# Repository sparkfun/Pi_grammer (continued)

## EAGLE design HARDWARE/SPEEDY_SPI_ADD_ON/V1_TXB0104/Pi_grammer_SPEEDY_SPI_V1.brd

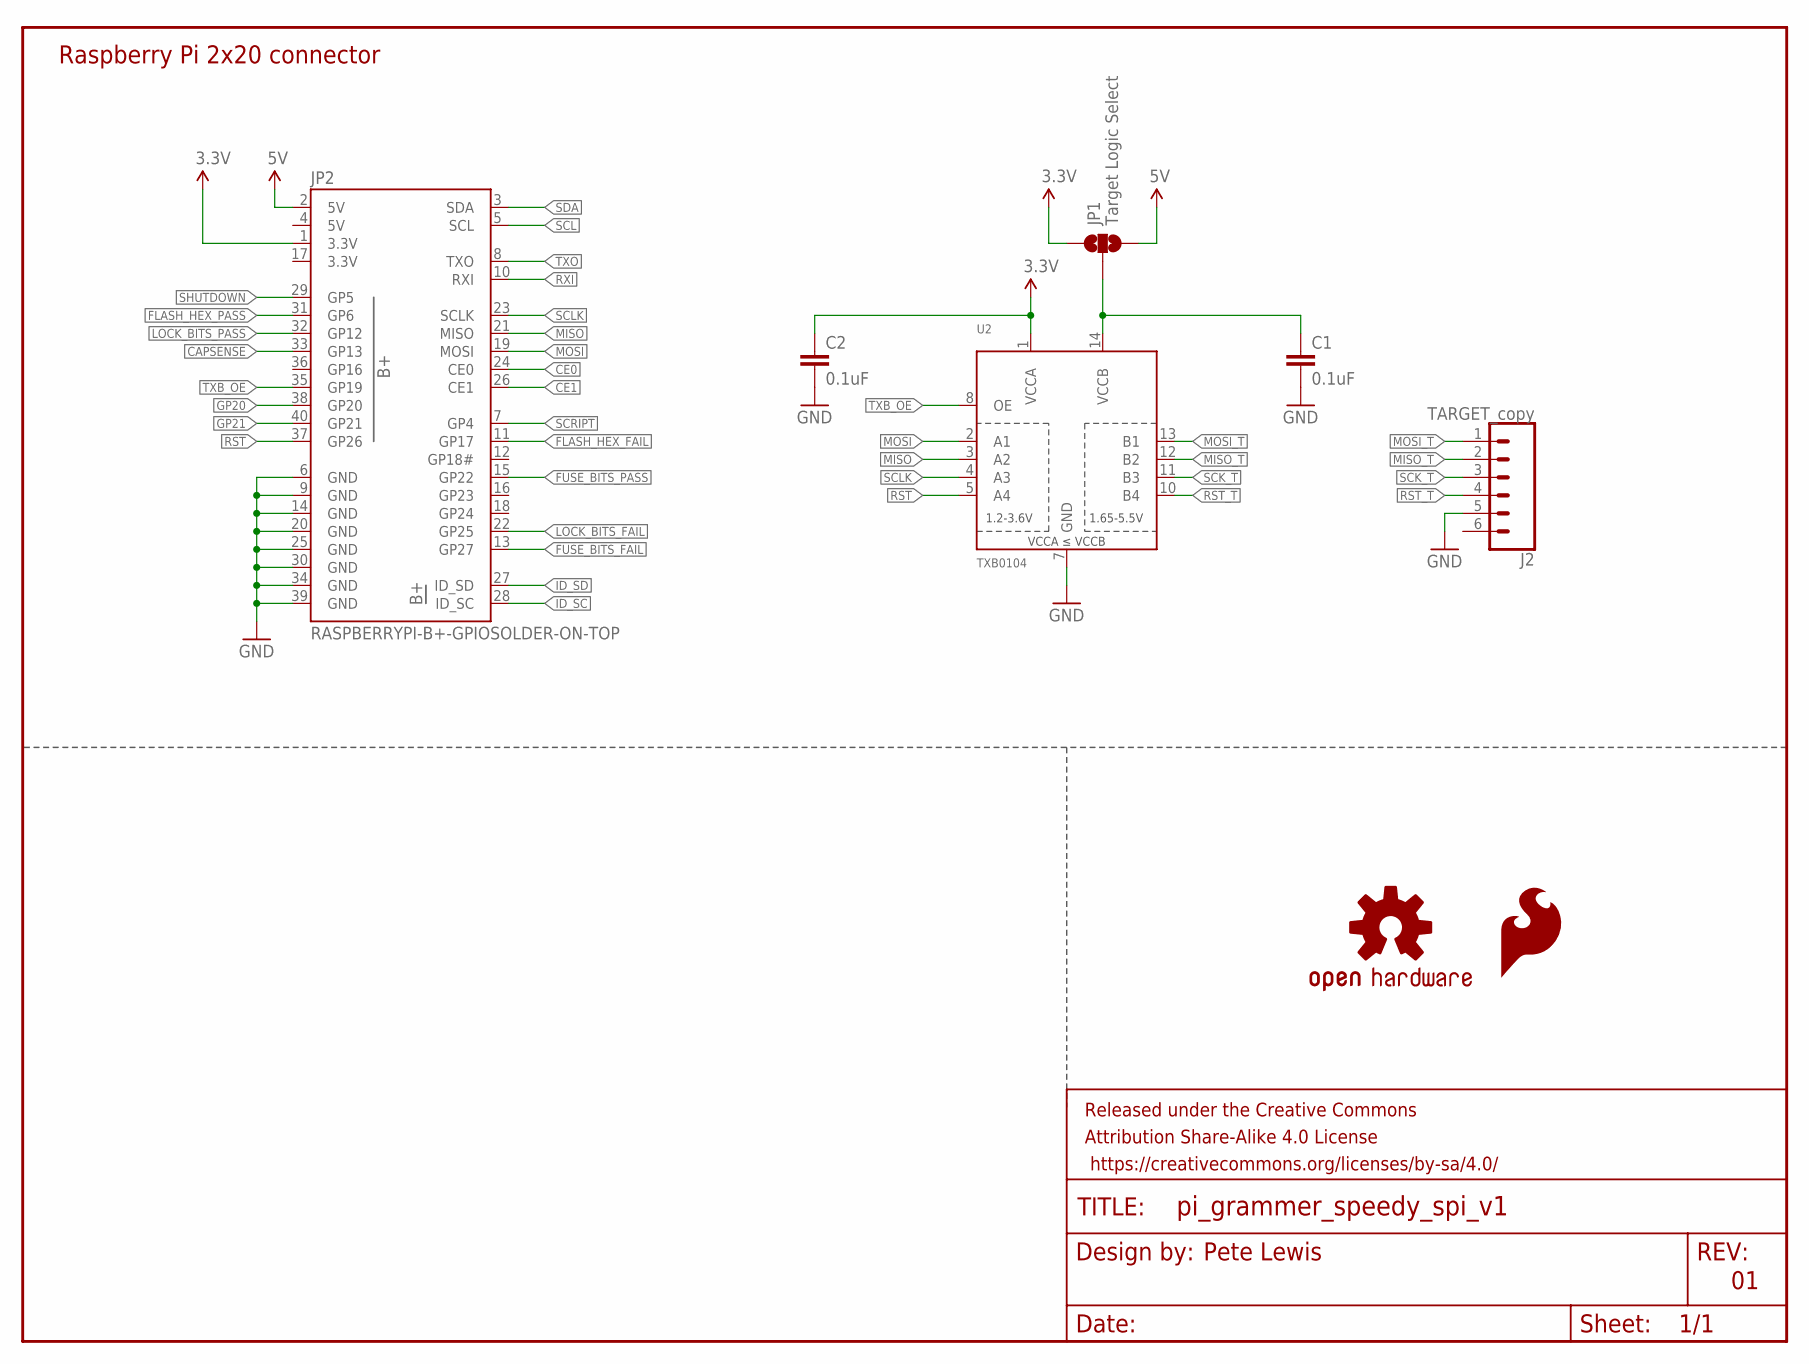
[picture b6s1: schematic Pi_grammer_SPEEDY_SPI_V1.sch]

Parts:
C1, C2: 0.1uF; 0603
FRAME1: FRAME-LETTER; CREATIVE_COMMONS
J2: TARGET_copy; MOLEX-1X6
JP1: Target Logic Select; SMT-JUMPER_3_NO_SILK
JP2: RASPBERRYPI-B+-GPIOSOLDER-ON-TOP; 2X20-SHROUDED-SOLDER-ON-TOP
LOGO1: SFE_LOGO_FLAME.1_INCH; SFE_LOGO_FLAME_.1
LOGO2: OSHW-LOGOS; OSHW-LOGO-S
U2: TXB0104; SO14

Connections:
3.3V: C2.1, JP1.1, JP2.1 (3.3V), JP2.17 (3.3V), U2.1 (VCCA)
5V: JP1.3, JP2.2 (5V), JP2.4 (5V)
CAPSENSE: JP2.33 (GP13)
CE0: JP2.24 (CE0)
CE1: JP2.26 (CE1)
FLASH_HEX_FAIL: JP2.11 (GP17)
FLASH_HEX_PASS: JP2.31 (GP6)
FUSE_BITS_FAIL: JP2.13 (GP27)
FUSE_BITS_PASS: JP2.15 (GP22)
GND: C1.2, C2.2, J2.5, JP2.6 (GND), JP2.9 (GND), JP2.14 (GND), JP2.20 (GND), JP2.25 (GND), JP2.30 (GND), JP2.34 (GND), JP2.39 (GND), U2.7 (GND)
GP20: JP2.38 (GP20)
GP21: JP2.40 (GP21)
ID_SC: JP2.28 (ID_SC)
ID_SD: JP2.27 (ID_SD)
LOCK_BITS_FAIL: JP2.22 (GP25)
LOCK_BITS_PASS: JP2.32 (GP12)
MISO: JP2.21 (MISO), U2.3 (A2)
MISO_T: J2.2, U2.12 (B2)
MOSI: JP2.19 (MOSI), U2.2 (A1)
MOSI_T: J2.1, U2.13 (B1)
unnamed: C1.1, JP1.2, U2.14 (VCCB)
RST: JP2.37 (GP26), U2.5 (A4)
RST_T: J2.4, U2.10 (B4)
RXI: JP2.10 (RXI)
SCK_T: J2.3, U2.11 (B3)
SCL: JP2.5 (SCL)
SCLK: JP2.23 (SCLK), U2.4 (A3)
SCRIPT: JP2.7 (GP4)
SDA: JP2.3 (SDA)
SHUTDOWN: JP2.29 (GP5)
TXB_OE: JP2.35 (GP19), U2.8 (OE)
TXO: JP2.8 (TXO)

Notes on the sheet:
Raspberry Pi 2x20 connector
Pete Lewis

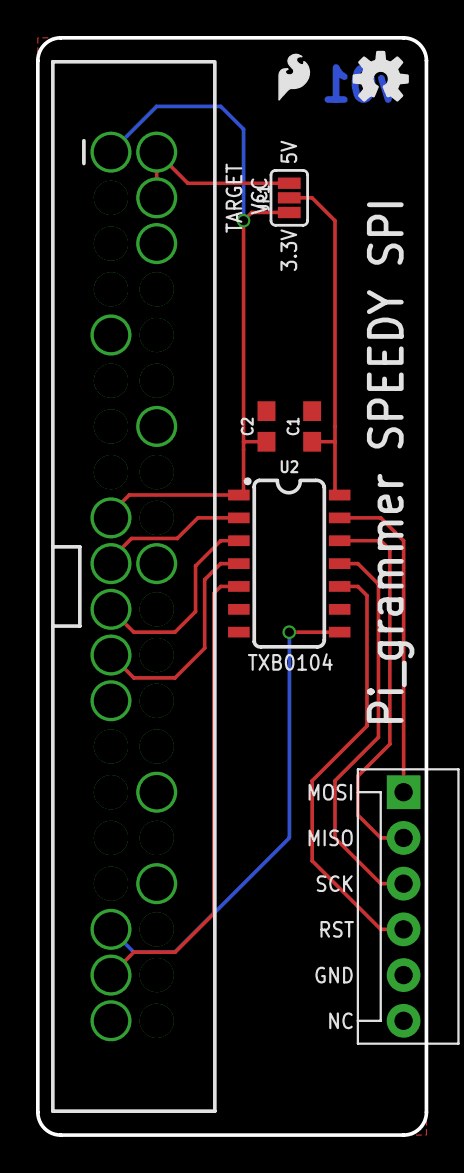
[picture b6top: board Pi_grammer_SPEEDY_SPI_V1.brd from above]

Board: 2 copper layers, 21.6 x 61.0 mm, 9 parts (0 on the bottom side), 13 nets.

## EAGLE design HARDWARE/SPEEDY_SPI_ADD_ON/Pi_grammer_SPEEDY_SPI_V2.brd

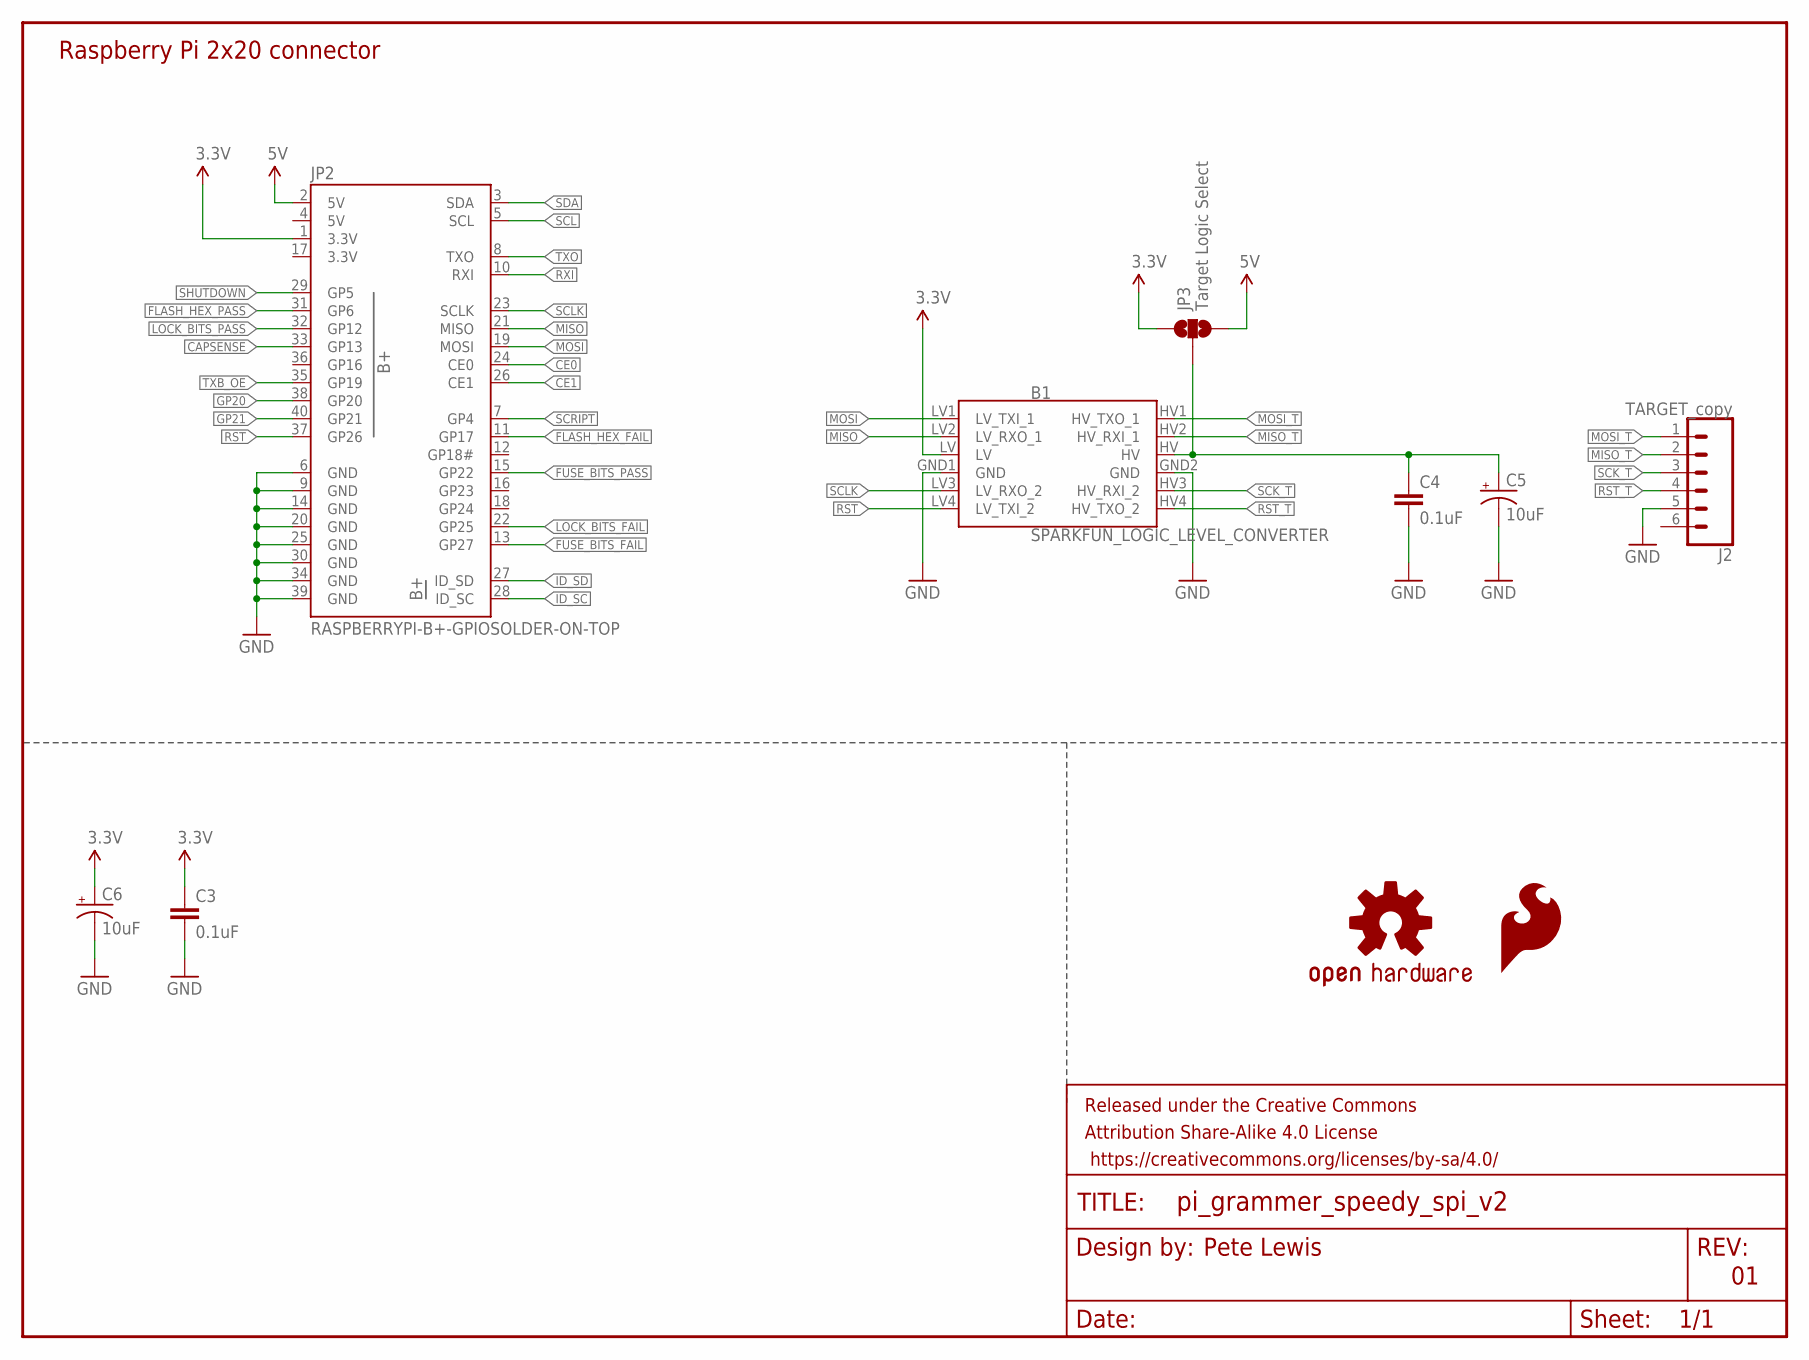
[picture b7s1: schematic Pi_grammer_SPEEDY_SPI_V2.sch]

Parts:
B1: SPARKFUN_LOGIC_LEVEL_CONVERTER
C3, C4: 0.1uF; 0603
C5, C6: 10uF; EIA3216
FRAME1: FRAME-LETTER; CREATIVE_COMMONS
J2: TARGET_copy; MOLEX-1X6_LOCK
JP2: RASPBERRYPI-B+-GPIOSOLDER-ON-TOP; 2X20-SHROUDED-SOLDER-ON-TOP
JP3: Target Logic Select; SMT-JUMPER_3_NO_SILK
LOGO1: SFE_LOGO_FLAME.1_INCH; SFE_LOGO_FLAME_.1
LOGO2: OSHW-LOGOS; OSHW-LOGO-S

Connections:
3.3V: B1.LV, C3.1, C6.+, JP2.1 (3.3V), JP2.17 (3.3V), JP3.1
5V: JP2.2 (5V), JP2.4 (5V), JP3.3
CAPSENSE: JP2.33 (GP13)
CE0: JP2.24 (CE0)
CE1: JP2.26 (CE1)
FLASH_HEX_FAIL: JP2.11 (GP17)
FLASH_HEX_PASS: JP2.31 (GP6)
FUSE_BITS_FAIL: JP2.13 (GP27)
FUSE_BITS_PASS: JP2.15 (GP22)
GND: B1.GND1 (GND), B1.GND2 (GND), C3.2, C4.2, C5.-, C6.-, J2.5, JP2.6 (GND), JP2.9 (GND), JP2.14 (GND), JP2.20 (GND), JP2.25 (GND), JP2.30 (GND), JP2.34 (GND), JP2.39 (GND)
GP20: JP2.38 (GP20)
GP21: JP2.40 (GP21)
ID_SC: JP2.28 (ID_SC)
ID_SD: JP2.27 (ID_SD)
LOCK_BITS_FAIL: JP2.22 (GP25)
LOCK_BITS_PASS: JP2.32 (GP12)
MISO: B1.LV2 (LV_RXO_1), JP2.21 (MISO)
MISO_T: B1.HV2 (HV_RXI_1), J2.2
MOSI: B1.LV1 (LV_TXI_1), JP2.19 (MOSI)
MOSI_T: B1.HV1 (HV_TXO_1), J2.1
unnamed: B1.HV, C4.1, C5.+, JP3.2
RST: B1.LV4 (LV_TXI_2), JP2.37 (GP26)
RST_T: B1.HV4 (HV_TXO_2), J2.4
RXI: JP2.10 (RXI)
SCK_T: B1.HV3 (HV_RXI_2), J2.3
SCL: JP2.5 (SCL)
SCLK: B1.LV3 (LV_RXO_2), JP2.23 (SCLK)
SCRIPT: JP2.7 (GP4)
SDA: JP2.3 (SDA)
SHUTDOWN: JP2.29 (GP5)
TXB_OE: JP2.35 (GP19)
TXO: JP2.8 (TXO)

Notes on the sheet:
Raspberry Pi 2x20 connector
Pete Lewis

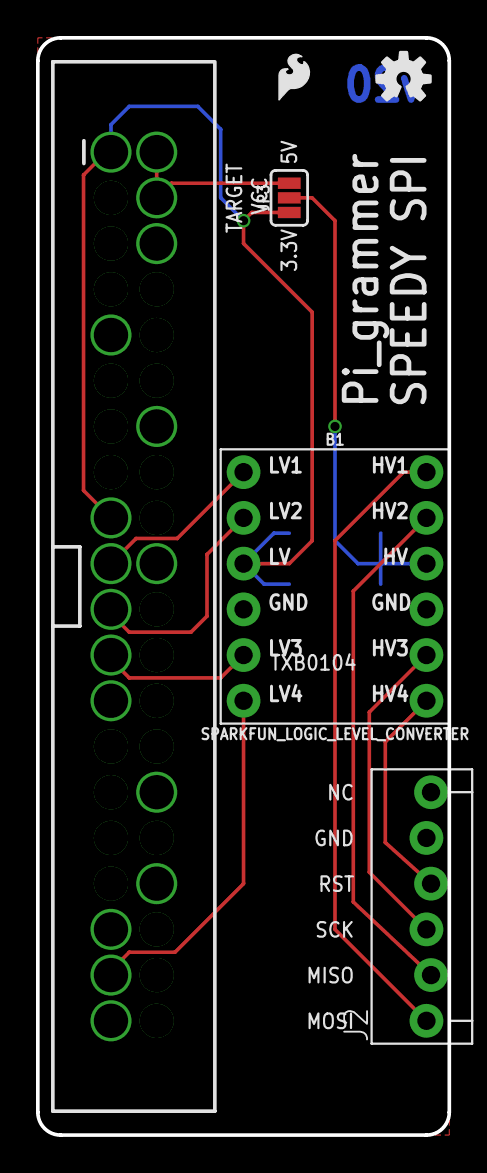
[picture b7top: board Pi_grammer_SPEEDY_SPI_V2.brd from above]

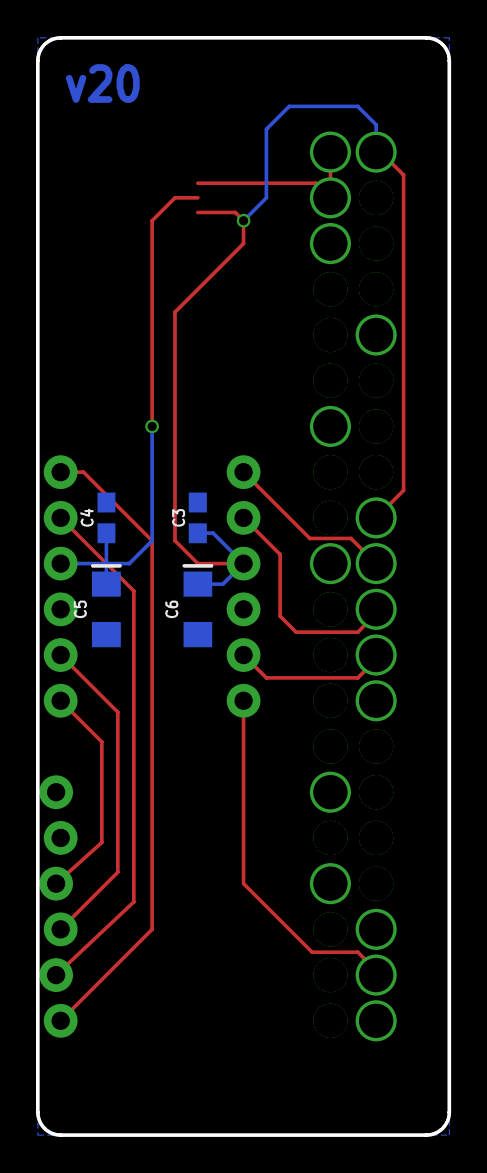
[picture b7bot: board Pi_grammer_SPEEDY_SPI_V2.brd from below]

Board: 2 copper layers, 22.9 x 61.0 mm, 11 parts (4 on the bottom side), 12 nets.

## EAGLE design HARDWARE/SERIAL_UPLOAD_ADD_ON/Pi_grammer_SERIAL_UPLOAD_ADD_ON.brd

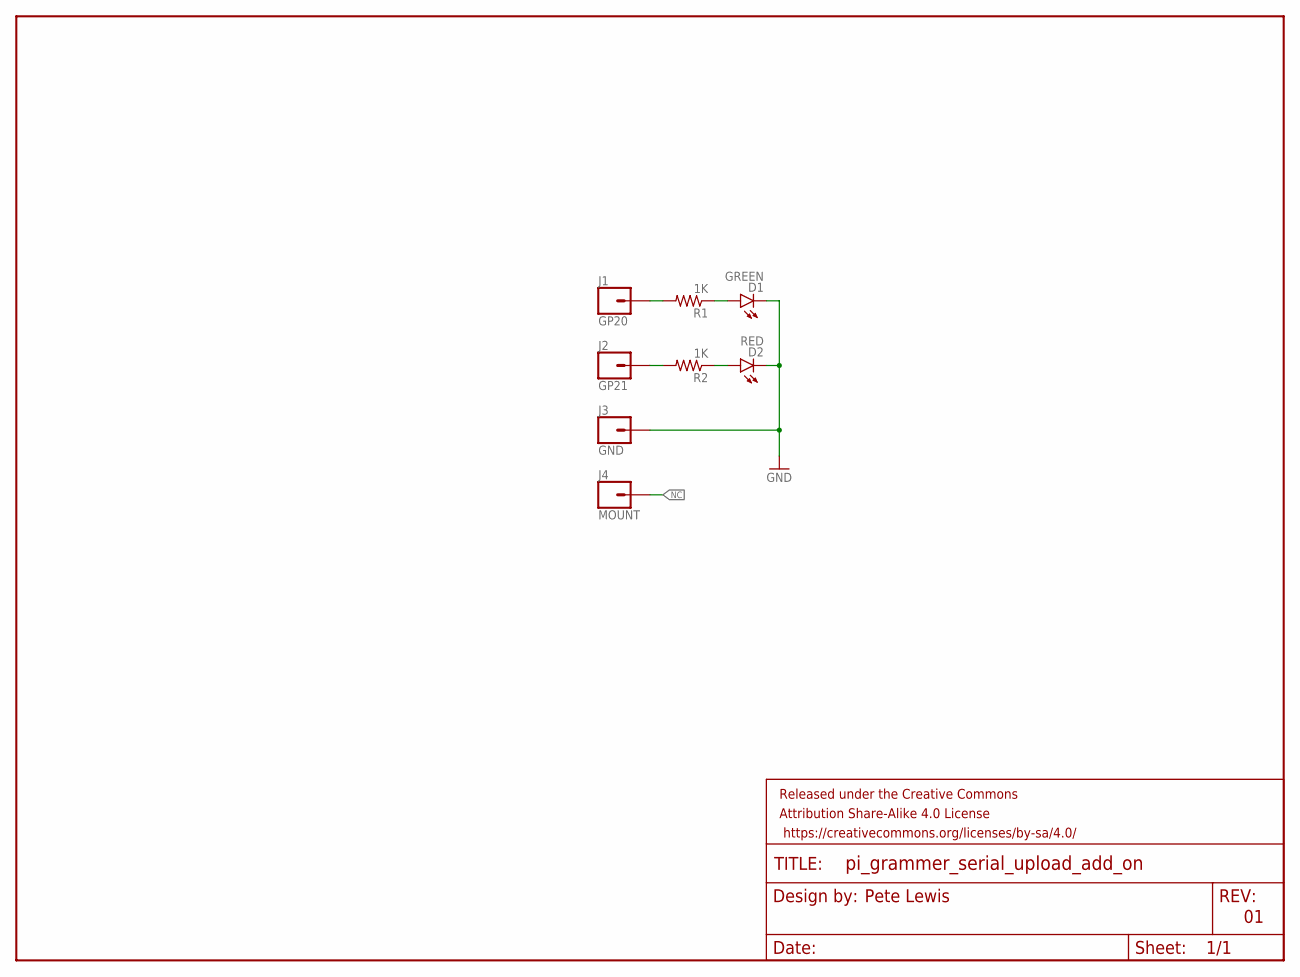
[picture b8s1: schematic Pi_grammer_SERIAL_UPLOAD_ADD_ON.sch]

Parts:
D1: GREEN; LED-1206
D2: RED; LED-1206
FRAME1: FRAME-LETTER; CREATIVE_COMMONS
J1: GP20; 1X01
J2: GP21; 1X01
J3: GND; 1X01
J4: MOUNT; 1X01
R1, R2: 1K; 0603-RES

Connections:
GND: D1.C, D2.C, J3.1
unnamed: J1.1, R1.2
unnamed: J2.1, R2.2
unnamed: D1.A, R1.1
unnamed: D2.A, R2.1
NC: J4.1

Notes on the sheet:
Pete Lewis

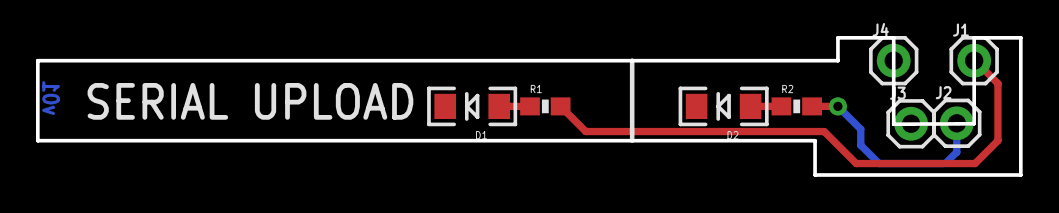
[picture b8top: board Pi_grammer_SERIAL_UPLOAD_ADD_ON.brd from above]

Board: 2 copper layers, 54.6 x 7.6 mm, 9 parts (0 on the bottom side), 5 nets.

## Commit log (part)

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2016-07-06 initial commit, hardware still needs routing
    includes some of the necessary files that go onto the Raspberry Pi.
2016-07-06 read this for info :)
2016-07-06 adding keywords
2016-07-06 added silk labeling to isp header pins
2016-07-06 routed
    also added .job and .pro to gitignore - eagle auto routing files
2016-07-08 updating to work with new shield hardware
    updated GPIO assignment for all LEDs.
    removed old LED assignments and related function calls
    created all_leds_off() funtion for use during programming cycle
    updated "main" while loop at the end to also watch the capsense net, and
    engage programming. Tweeked the counter amounts for snappy response.
    Added LED control to end of parse_results() function, to indicate
2016-07-13 changes "script running" led silk to "STAT"
2016-08-05 updated to complete paths
    When it launched from rc.local, it needed this.
2016-08-05 complete paths, clean results, added "sh" to command
    the "sh" prior to the command sends any readout from prompt to the tty1
    - which I learned you can view by pressing crtl alt F1. Note Crtl Alt F7
    will talk you back to the desktop.
    Added blink cirle to indicate firmware update
    added delete old firmware files beofre the copy from media happens
    Made the repsonse a bit more snappy with the new stat counter, and made
2016-08-16 PROD_IDs to all populated parts, SCH cleanup
2016-08-18 added fiducials
2016-08-22 bash file cleanup - also added fuse/lock variables
    for easier setup/editing
2016-08-22 internal pullup on shutdown, also added delay at startup
2016-08-25 Some standard pics for documentation
2016-08-25 Moved into separate folders
2016-08-26 adding setup instructions
    This document shows how to setup a pi_grammer to use a specific hex file
    and bash file for programming.
    Note, this does not document how to setup a Pi image from scratch, these
    instructions rely on having a pre-programmed uSD card with the "generic
    Pi_grammer" image.
2016-09-02 Flash size now finds with larger files
    When programming a mega, the flash size can contain one more character,
    so I had to use line.find tool to get the trimming of the line correct.
2016-09-08 Added Serial upload capability
    This will now call "/home/pi/SERIAL_UPLOAD/pi_serial_upload.sh" after
    programming fuse/bootloader(hex)/lock.
    Note, it will only call this serial upload bash file if the file
    exisits. I added this in so that this "test.py" python will work with
    programming jigs that don't require serial uploading.
2016-09-12 Serial Upload to reference on MAIN board.
    Planning ot make a little "add on" board to drop on top of the MAIN
    board. It will provide serial upload success/fail LEDs off of GPIO 20
    and 21. The idea is to have castellated edge PTH pins to connect to the
    bottom 4 pins of the 2x20 connector. We really only need GND and the two
    GPs, but I figured 4 will provide better stability.
2016-09-27 Added "-i 1000"
    Added in a "bitbang delay" into the AVRDUDE call for fuse bits. This
    slows down the communication speed - ensureing we are well below what
    some fresh chips need (if it's operating on internal oscilator at 1MHz,
    then we need it to be SUB 125KHz).
    Looking at the logic analyzer I see it's programming fuse bits at about
    370 Hz (yes HERTZ, not KILO Hertz). This is plenty slow.
2016-10-25 ESP32 programming dev
    Modified test.py to parse for successful readout of flash programming of
    ESP32 chip.
    Also, the pi_program.sh example uses python tool with flags for
    programming esp32 chips, it dumps the command prompt readoud "aka 1>" to
    the flash_results.txt file for later parsing.
2016-10-25 example bash for esp32 programming
2017-03-14 FUSE BITS options; EXT FUSE: 0x07 = 0xFF
    Working on the Big Time programming. It called for EXT fuse to be 0xFF,
    and I had to modify it to 0x07 to work with AVR dude (due to
    bitmasking).
2017-04-18 adding in support for linuxspi
    need this as an option in the config file.
    NOTE RESET IS ON GPIO PIN 25 - this may need to change
2017-04-18 spi on pi setup instructions
2017-04-19 hard reset via direct gpio control
    I was seeing strange behavior with fresh boards on the microview ganged
    programmer. It would successfully program fuses, but then always fail to
    enter programming mode for the flash programming step. It worked fine if
    you tried once, reset power to boards, then programmed a second time.
    Also, note it was working fine with first time programming on fresh ICs
    with the older GPIO bit banging programmer method (although really
2017-04-19 adapter soldering instructions
    This is how we can use our exhisting hardware "v10" to use linuxSPI tru
    hardware pins.
2017-04-27 SPEED SPI layout work
    locking footprint on converter.
    moved to 16 mils traces everywhere.
    curved traces to keep length of data lines as similar as possible.
    removed pin 20 GND on PI header. Not necessary and wanted more clearance
    from nearby data trace.
2017-04-27 Option to "tap" logic level from target
    Note, this required a modification to the ADAPTER as well. I am
    utilizing pin 6 on the 1x6 pin header (jumper wire) to transfer VCC back
    to the logic level converter.
    I'm not sure why on the original design I didn't think to include VCC in
    the comm lines to the target - I think it was because the raspi doesn't
    have any ADCs to actually verify it, so I didn't know if it was worth
2017-04-28 Speedy SPI library work
    updated device to only include pins/pads that are used. added in actual
    drill hits for the unused pads.
    rduced down to only 2 GND connections.
    reduce isolate to 10 mils to allow for GND flow across header pins.
2017-05-26 Speedy SPI corrections
    Extended out to the right, and scooted all components to clear current
    Pi_grammer "hat" design.
    On V2, I had to solder all of the PTH pins flush on the bottom, and the
    SMD parts below the LLC get in the way.
2017-06-20 SPI pins and llc
    Just SCH work at this point.
2017-06-28 capsense IC replacement
    trying out the UDFN package - dang that's tiny
2017-06-28 finished layout v20
2017-07-14 Serial upload working for RedBoards
    Note, I had to install arduino onto the Pi. And then I just watched
    verbose debug while using the IDE and copied the avrdude calls. See
    /SERIAL_UPLOAD/readme.txt for more info.
    Also adjusted/added to the test.py module. It now has a proper
    parse_results_serial() function to verify that the target was written to
    (although I omitted actual hex read-back verification to save time).
2017-11-17 Serial upload stuff
    Added in LOCK_BITS_PASS variable so that I can avoid attempting a serial
    upload if there is any failures upstream.
    Also, started checking a "temp" copy of readout from serial program, to
    adetify if it's looking hopeful. If it's going to fail, then it usually
    takes about 30 seconds to timeout, and can appear to the tech that the
    pi_grammer has frozen. This helps avoid this illusion.
2017-12-14 fixing clean_results bug
    If you are not using the SERIAL_UPLOAD feature, it will no longer try to clean up that file.
    Note, previously, it would try to truncate a file that doesn't exist and lock up the program :(
    fixed now!!
2017-12-18 pi_grammer shell script $CHIP variable
    Added a "CHIP" variable to the script that holds the chip to be
    programmed. Saves us a small amount of time not updating both fush and
    flash individually. Changed in both linuxspi folder and in the main file
    structure.
2017-12-21 pi_serial_upload default settings and variables
    I added a device and baud rate to the top of this script similar to the
    pi_upload shell script. I changed the programmer command (-c) to default
    to arduino instead of wiring, the default device to atmega328p, and the
    baud to 115200. I also put notes in the script to pick a slower baud
    rate for slower clock speesd ( <= 8mHz)
2017-12-22 Auto update test.py
    If you put a new test.py file on a media device, then plug it into the pi_grammer, it will now pull that in and overwrite the local test.py file.
    Still need to create a RE-launching of python with the new test.py... coming soon.
2017-12-22 need this sh file for the actual relaunch
    must be saved in the home/pi/ folder
2017-12-28 Re-creating pi_program on Raspi to avoid strange CR behavior
    Note, I was seeing some errors being thrown in the raspi when I tried to run pi_program.sh - it was showing that the command "sleep 0.1\r" was an invalid value for sleep. I'm assuming that the "\r" i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
    Added comments around the device variable
2018-01-03 Adding useful desktop links
    I find myself typing in these three commands a lot, so I turned them into double-click-able "links" that you can copy to the desktop.
    The shell files themselves (the ".sh" files) must live in /home/pi/Pi_grammer_utililties
    And you must copy the desktop link files to you desktop.
2018-01-19 on serial upload failure - added killall avrdude
    When serial upload fails, it will take FOREVER for avrdude to attempt (like 10 times) to serial upload, and it will timeout on each of those attempts. Rather than waiting for that to finish (which lo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
    Also note, in the previous test.py, even though the python module would move on, the avrdude instance would continue. This would lock up the com port
2018-02-13 Default images for v20 - includes serial LED
2018-03-08 Update README.md
    Add tutorial link. =)
2018-03-16 adding instruction to get to pi_grammer from NOOBs
    note, this is not tested yet, but I'm 99% sure this is all you need to do. Will test ASAP.
2018-03-23 optional delay before serial program
    Note, this is commented out by default, but will be needed for doing any serial programming to micros that need a sec to enumerate the com port. See the following comment thread on the tutorial for m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
    [https://learn.sparkfun.com/tutorials/raspberry-pi-stand-alone-programmer/discuss#comment-5ab2d42d7e7fa89f378b4567](https://learn.sparkfun.com/tutorials/raspberry-pi-stand-alone-programmer/discuss#co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
2018-03-29 pi_grammer v21
    Added in isolation switch
2018-03-29 deleting old ADD ON boards
    These are now baked into the MAIN board v21
2018-04-20 Swapped out package to paste-closed jumper for TARGET VCC
    This needed a default target logic select. It is now closed (selected) via paste on the "TARGET VCC" option.
2018-04-24 correcting adapter name to "AVR_ADAPTER"
2018-04-24 pi_grammer_MAIN updates for storefront product
    -moved to RA SMT 1x6 header for programming lines to cable, had to re-route a few things, MISO and MOSI have a much better direct route now.
    -Enlarged most silk to standard 0.05
    -changed text silk on "blank boxes" to more generic use case terms - project name, version, date etc.
    -added prod ID to switch IC
    -updated copper and sch version number to v22
    -added large sparkfun logo to bottom side silk
2018-04-25 updated switch (U2) to use sparkfun eagle library
    also updated all libraries and the LEDs silk changed to updated versions of 1206 packages
2018-04-25 schematic frame update to CC 4.0
2018-04-25 schematic cleanup and notes
2018-04-25 sch cleanup
2018-04-25 Selective solder path on layer 48
2018-04-25 measures on 47
2018-05-09 Changing program_serial command assignment
    The previous call to bash using 'sh' limits what the given bash script can execute. Changing it to 'bash' (superset of 'sh') allows for a greater range of functions available to use in executed scrip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
2018-05-21 Adjusted silk for new product name
    Also updated all silk to sweet buzzard style labels
2018-05-29 fixed hatch ground pour under capsense pad
    Due to inverted sPlace (silk), it was hard to see that the hatched GND was actually gone. I must have ripped up a "floating" GND trace that connects the hatched GND polygon to the main GND polygon on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
2018-05-30 panel v22 created
2018-07-13 bringing in optiboot and blink hexes - for easier access in the hookup guide
    Note, these hex files are used on the Redboard, and are simply here as examples and used in the hookup guide to show SPI programming and a serial upload.
2018-07-27 Pogo adapter - Follows SFE pinout
